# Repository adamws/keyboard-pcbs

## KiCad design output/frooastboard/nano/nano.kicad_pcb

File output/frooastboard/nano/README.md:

## frooastboard/nano

[layout](nano-kle.json) - [PCB](nano.kicad_pcb)

{:loading="lazy"}

[Open in keyboard-layout-editor](http://www.keyboard-layout-editor.com/##@@=0,0&=0,1;&@_c=#777777;&=1,0&_c=#cccccc;&=1,1)

{:loading="lazy"}

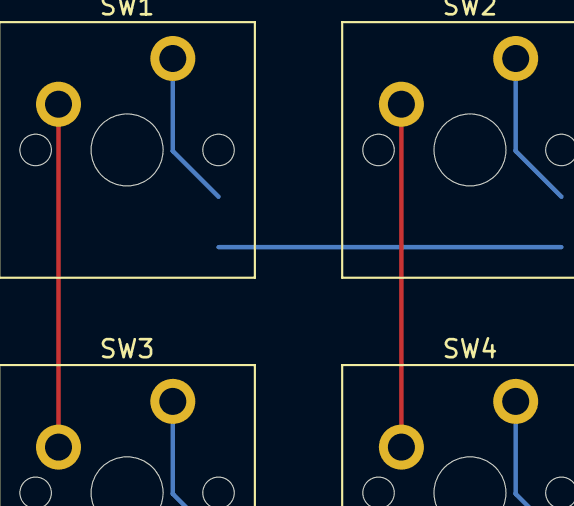
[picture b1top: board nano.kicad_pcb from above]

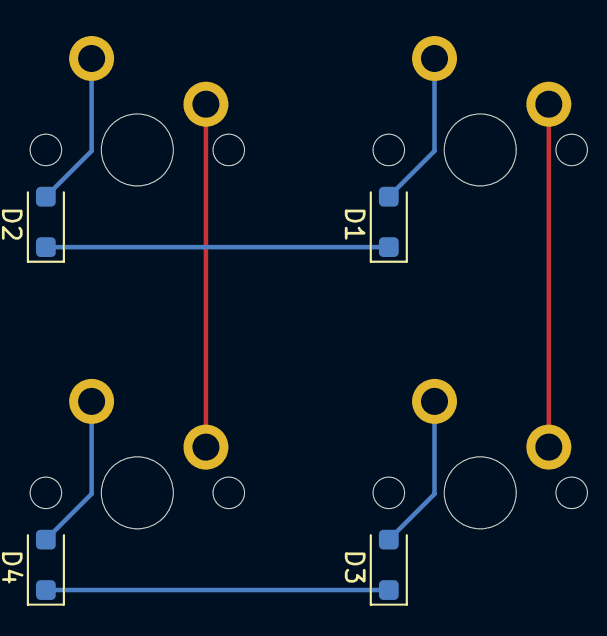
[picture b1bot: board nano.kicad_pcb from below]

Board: 2 copper layers, 8 parts (4 on the bottom side), 8 nets.

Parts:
D1, D2, D3, D4: D_SOD-123F
SW1, SW2, SW3, SW4: SW_Cherry_MX_PCB_1.00u

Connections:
COL0: SW1.1, SW3.1
COL1: SW2.1, SW4.1
unnamed: D1.2, SW1.2
unnamed: D2.2, SW2.2
unnamed: D3.2, SW3.2
unnamed: D4.2, SW4.2
ROW0: D1.1, D2.1
ROW1: D3.1, D4.1

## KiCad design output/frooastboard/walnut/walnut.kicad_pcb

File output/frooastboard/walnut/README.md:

## frooastboard/walnut

[layout](walnut-kle.json) - [PCB](walnut.kicad_pcb)

{:loading="lazy"}

[Open in keyboard-layout-editor](http://www.keyboard-layout-editor.com/##@@_c=#777777;&=0,0&_c=#cccccc;&=0,1&=0,2&=0,3&=0,4&=0,5&=0,6&=0,7&=1,0&=1,1&=1,2&=1,3&=1,4&_c=#aaaaaa&w:2;&=1,5&_x:0.5&c=#cccccc;&=5,5&=5,6&=5,7;&@_c=#aaaaaa&w:1.5;&=2,0&_c=#cccccc;&=2,1&=2,2&=2,3&=2,4&=2,5&=2,6&=2,7&=3,0&=3,1&=3,2&=3,3&=3,4&_x:0.25&c=#777777&w:1.25&h:2&w2:1.5&h2:1&x2:-0.25;&=3,5%0A%0A%0A0,0&_x:0.5&c=#cccccc;&=7,5&=7,6&=7,7;&@_c=#aaaaaa&w:1.75;&=4,0&_c=#cccccc;&=4,1&=4,2&=4,3&=4,4&=4,5&=4,6&=4,7&=5,0&=5,1&=5,2&=5,3&=5,4%0A%0A%0A0,0;&@_c=#aaaaaa&w:1.25;&=6,0%0A%0A%0A0,0&_c=#cccccc;&=6,1%0A%0A%0A0,0&=6,2&=6,3&=6,4&=6,5&=6,6&=6,7&=7,0&=7,1&=7,2&=7,3&_c=#aaaaaa&w:2.75;&=7,4&_x:1.5&c=#777777;&=3,6;&@_c=#aaaaaa&w:1.25;&=8,0&_w:1.25;&=8,1&_w:1.25;&=8,2&_c=#cccccc&w:6.25;&=8,3&_c=#aaaaaa&w:1.25;&=8,4&_w:1.25;&=8,5&_w:1.25;&=8,6&_w:1.25;&=8,7&_x:0.5&c=#777777;&=1,6&=3,7&=1,7;&@_x:13.5&y:-4&c=#cccccc&w:1.5;&=5,4%0A%0A%0A0,1;&@_x:12.75&c=#777777&w:2.25;&=3,5%0A%0A%0A0,1;&@_c=#aaaaaa&w:2.25;&=6,0%0A%0A%0A0,1)

{:loading="lazy"}

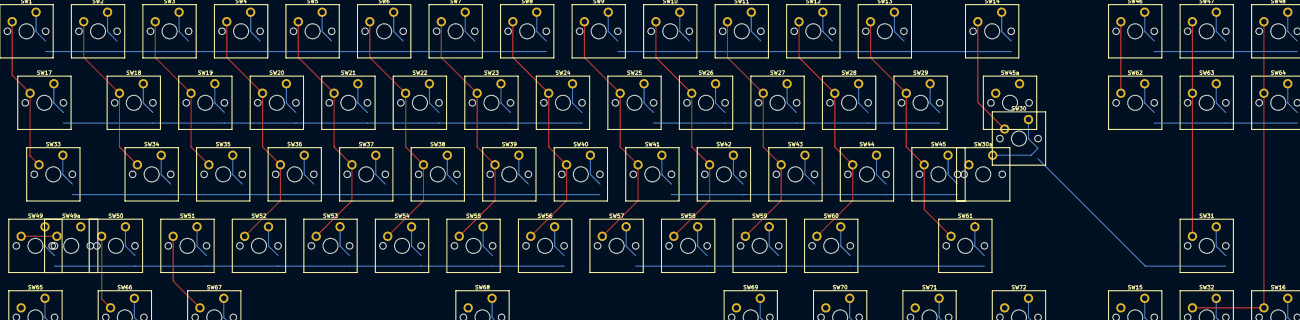
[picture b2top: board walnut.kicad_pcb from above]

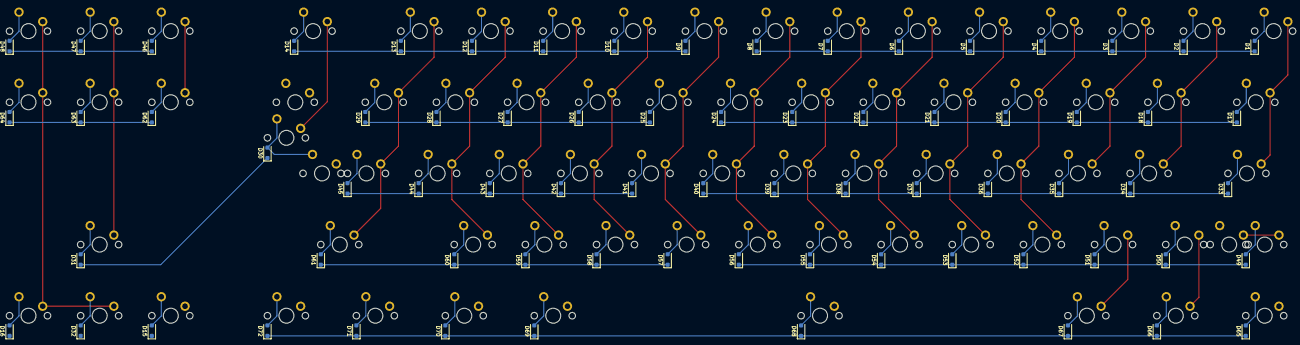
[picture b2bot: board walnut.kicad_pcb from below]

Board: 2 copper layers, 147 parts (72 on the bottom side), 89 nets.

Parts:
D1, D2, D3, D4, D5, D6, D7, D8, D9, D10, D11, D12, D13, D14, D15, D16, D17, D18, D19, D20, D21, D22, D23, D24, D25, D26, D27, D28, D29, D30, D31, D32, D33, D34, D35, D36, D37, D38, D39, D40, D41, D42, D43, D44, D45, D46, D47, D48, D49, D50, D51, D52, D53, D54, D55, D56, D57, D58, D59, D60, D61, D62, D63, D64, D65, D66, D67, D68, D69, D70, D71, D72: D_SOD-123F
SW1, SW2, SW3, SW4, SW5, SW6, SW7, SW8, SW9, SW10, SW11, SW12, SW13, SW14, SW15, SW16, SW17, SW18, SW19, SW20, SW21, SW22, SW23, SW24, SW25, SW26, SW27, SW28, SW29, SW30, SW30a, SW31, SW32, SW33, SW34, SW35, SW36, SW37, SW38, SW39, SW40, SW41, SW42, SW43, SW44, SW45, SW45a, SW46, SW47, SW48, SW49, SW49a, SW50, SW51, SW52, SW53, SW54, SW55, SW56, SW57, SW58, SW59, SW60, SW61, SW62, SW63, SW64, SW65, SW66, SW67, SW68, SW69, SW70, SW71, SW72: SW_Cherry_MX_PCB_1.00u

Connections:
COL0: SW1.1, SW9.1, SW17.1, SW25.1, SW33.1, SW41.1, SW49.1, SW49a.1, SW57.1, SW65.1
COL1: SW2.1, SW10.1, SW18.1, SW26.1, SW34.1, SW42.1, SW50.1, SW58.1, SW66.1
COL2: SW3.1, SW11.1, SW19.1, SW27.1, SW35.1, SW43.1, SW51.1, SW59.1, SW67.1
COL3: SW4.1, SW12.1, SW20.1, SW28.1, SW36.1, SW44.1, SW52.1, SW60.1, SW68.1
COL4: SW5.1, SW13.1, SW21.1, SW29.1, SW37.1, SW45.1, SW45a.1, SW53.1, SW61.1, SW69.1
COL5: SW6.1, SW14.1, SW22.1, SW30.1, SW30a.1, SW38.1, SW46.1, SW54.1, SW62.1, SW70.1
COL6: SW7.1, SW15.1, SW23.1, SW31.1, SW39.1, SW47.1, SW55.1, SW63.1, SW71.1
COL7: SW8.1, SW16.1, SW24.1, SW32.1, SW40.1, SW48.1, SW56.1, SW64.1, SW72.1
unnamed: D1.2, SW1.2
unnamed: D2.2, SW2.2
unnamed: D3.2, SW3.2
unnamed: D4.2, SW4.2
unnamed: D5.2, SW5.2
unnamed: D6.2, SW6.2
unnamed: D7.2, SW7.2
unnamed: D8.2, SW8.2
unnamed: D9.2, SW9.2
unnamed: D10.2, SW10.2
unnamed: D11.2, SW11.2
unnamed: D12.2, SW12.2
unnamed: D13.2, SW13.2
unnamed: D14.2, SW14.2
unnamed: D15.2, SW15.2
unnamed: D16.2, SW16.2
unnamed: D17.2, SW17.2
unnamed: D18.2, SW18.2
unnamed: D19.2, SW19.2
unnamed: D20.2, SW20.2
unnamed: D21.2, SW21.2
unnamed: D22.2, SW22.2
unnamed: D23.2, SW23.2
unnamed: D24.2, SW24.2
unnamed: D25.2, SW25.2
unnamed: D26.2, SW26.2
unnamed: D27.2, SW27.2
unnamed: D28.2, SW28.2
unnamed: D29.2, SW29.2
unnamed: D30.2, SW30.2, SW30a.2
unnamed: D31.2, SW31.2
unnamed: D32.2, SW32.2
unnamed: D33.2, SW33.2
unnamed: D34.2, SW34.2
unnamed: D35.2, SW35.2
unnamed: D36.2, SW36.2
unnamed: D37.2, SW37.2
unnamed: D38.2, SW38.2
unnamed: D39.2, SW39.2
unnamed: D40.2, SW40.2
unnamed: D41.2, SW41.2
unnamed: D42.2, SW42.2
unnamed: D43.2, SW43.2
unnamed: D44.2, SW44.2
unnamed: D45.2, SW45.2, SW45a.2
unnamed: D46.2, SW46.2
unnamed: D47.2, SW47.2
unnamed: D48.2, SW48.2
unnamed: D49.2, SW49.2, SW49a.2
unnamed: D50.2, SW50.2
unnamed: D51.2, SW51.2
unnamed: D52.2, SW52.2
unnamed: D53.2, SW53.2
unnamed: D54.2, SW54.2
unnamed: D55.2, SW55.2
unnamed: D56.2, SW56.2
unnamed: D57.2, SW57.2
unnamed: D58.2, SW58.2
unnamed: D59.2, SW59.2
unnamed: D60.2, SW60.2
unnamed: D61.2, SW61.2
unnamed: D62.2, SW62.2
unnamed: D63.2, SW63.2
unnamed: D64.2, SW64.2
unnamed: D65.2, SW65.2
unnamed: D66.2, SW66.2
unnamed: D67.2, SW67.2
unnamed: D68.2, SW68.2
unnamed: D69.2, SW69.2
unnamed: D70.2, SW70.2
unnamed: D71.2, SW71.2
unnamed: D72.2, SW72.2
ROW0: D1.1, D2.1, D3.1, D4.1, D5.1, D6.1, D7.1, D8.1
ROW1: D9.1, D10.1, D11.1, D12.1, D13.1, D14.1, D15.1, D16.1
ROW2: D17.1, D18.1, D19.1, D20.1, D21.1, D22.1, D23.1, D24.1
ROW3: D25.1, D26.1, D27.1, D28.1, D29.1, D30.1, D31.1, D32.1
ROW4: D33.1, D34.1, D35.1, D36.1, D37.1, D38.1, D39.1, D40.1
ROW5: D41.1, D42.1, D43.1, D44.1, D45.1, D46.1, D47.1, D48.1
ROW6: D49.1, D50.1, D51.1, D52.1, D53.1, D54.1, D55.1, D56.1
ROW7: D57.1, D58.1, D59.1, D60.1, D61.1, D62.1, D63.1, D64.1
ROW8: D65.1, D66.1, D67.1, D68.1, D69.1, D70.1, D71.1, D72.1
